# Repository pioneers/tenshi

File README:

Pioneers in Engineering Control System Next

STUFF

--------------------------------------------------------------------------------
- Hints for compiling and running                                              -
--------------------------------------------------------------------------------

Are you on Ubuntu? Use install_build_deps.sh! (You must be connected to the
Internet for this to work.) After running install_build_deps.sh, you also need
to manually:
1) Run emcc. This creates some config files necessary for it to work.
2) Run EAGLE. This creates a directory in your home so that it doesn't prompt
   you while building (and stalling the build).

Compile using ./build.sh. Build results are in build/artifacts.

Run angel-player using ./run-angel-player (build.sh is not needed in this
case).

Things needed for compiling:
* coreutils, build-essential, etc.
* tar, bz2, etc.
* python (2.7 recommended)
* nodejs (currently using v0.10.26, from the chris-lea/node.js PPA)
* wget
* pep8
* jshint (install from npm, currently using 2.1.11)
* csslint (install from npm, currently using 0.10.0)
* project-tenshi-tools (get from Jenkins)
* emscripten (get from http://rqou.com/emscripten-bin-18apr2014.tar.bz2)
* avr-gcc (currently using the nonolith/avr-toolchain PPA)
* libX11, Xvfb
* EAGLE (currently using v6.5.0)
* Java JRE
* PyYAML

Running Angel Player: It is recommended to have a separate copy of xulrunner
located somewhere such as your home directory. The command you would need to use
would be something like:
~/xulrunner/xulrunner angel-player/src/application.ini -jsconsole -purgecaches

-purgecaches is required in order to debug JS in-tree (without building and
updating build ID).

If you are running on Ubuntu, make sure to add yourself to the dialout group to
access your USB serial port (usually /dev/ttyUSB0).

Setting up Angel Player debugger:
Angel Player can be debugged by using the Firefox remote debug tools that are
normally used to debug Thunderbird/Firefox OS. To enable this on the Firefox
side:
1. Open the developer tools (Ctrl+Shift+I)
2. Click the "Settings" sprocket in the top-left.
3. Under advanced, enable remote debugging (you may also need to enable chrome
   debugging).

To enable remote debugging in Angel Player, either launch the in-tree version
of the code or set "devtools.debugger.remote-enabled" and
"devtools.chrome.enabled" to "true" in about:config. If for some reason you
already have an application listening on port 6000 on your computer, you can
also change "devtools.debugger.remote-port" to an alternate port.

To connect the remote debugger, select "Tools>Web Developer>Connect..." in
Firefox. Set the host to localhost and the port to 6000 (unless you changed
the port above) and click connect. Until this is fixed, to debug JS, select
"Main Process" and to debug CSS select "chrome://angel-player/content/main.html"

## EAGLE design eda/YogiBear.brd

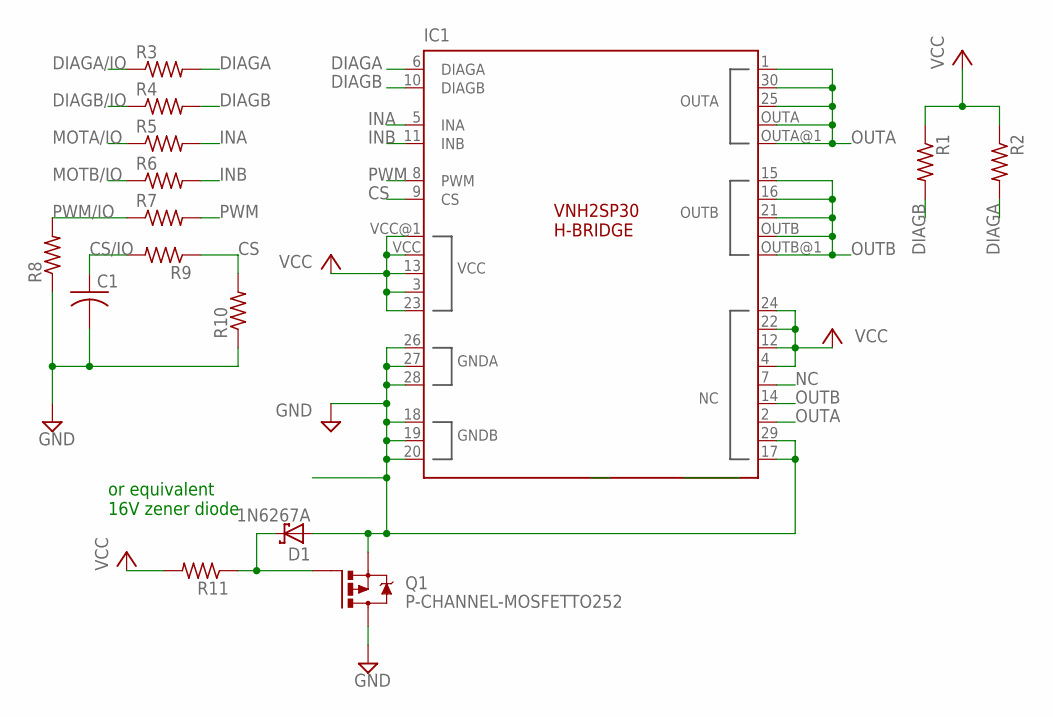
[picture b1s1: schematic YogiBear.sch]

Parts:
C1: C-US025-024X044; C025-024X044
D1: 1N6267A; C4111-15
IC1: VNH2SP30
Q1: P-CHANNEL-MOSFETTO252; TO252
R1, R2, R3, R4, R5, R6, R7, R8, R9, R10, R11: R-US_R0603; R0603

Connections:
CS: IC1.9 (CS), R9.1, R10.2
CS/IO: C1.1, R9.2
DIAGA: IC1.6 (DIAGA), R2.2, R3.2
DIAGA/IO: R3.1
DIAGB: IC1.10 (DIAGB), R1.2, R4.2
DIAGB/IO: R4.1
GND: C1.2, D1.A, IC1.17 (NC), IC1.18 (GNDB), IC1.19 (GNDB), IC1.20 (GNDB), IC1.26 (GNDA), IC1.27 (GNDA), IC1.28 (GNDA), IC1.29 (NC1), Q1.2 (S), Q1.3 (D), R8.1, R10.1
INA: IC1.5 (INA), R5.2
INB: IC1.11 (INB), R6.2
MOTA/IO: R5.1
MOTB/IO: R6.1
unnamed: D1.C, Q1.1 (G), R11.1
NC: IC1.7 (NC4)
OUTA: IC1.1 (OUTA), IC1.2 (NC2), IC1.25 (OUTA), IC1.30 (OUTA), IC1.OUTA, IC1.OUTA@1 (OUTA)
OUTB: IC1.14 (NC3), IC1.15 (OUTB), IC1.16 (OUTB), IC1.21 (OUTB), IC1.OUTB, IC1.OUTB@1 (OUTB)
PWM: IC1.8 (PWM), R7.2
PWM/IO: R7.1, R8.2
VCC: IC1.3 (VCC), IC1.13 (VCC), IC1.23 (VCC), IC1.VCC, IC1.VCC@1 (VCC), R1.1, R2.1, R11.2
VIN: IC1.4 (NC5), IC1.12 (NC6), IC1.22 (NC7), IC1.24 (NC8)

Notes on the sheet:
or equivalent 16V zener diode

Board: 2 copper layers, 15 parts (0 on the bottom side), 14 nets, no tracks yet.

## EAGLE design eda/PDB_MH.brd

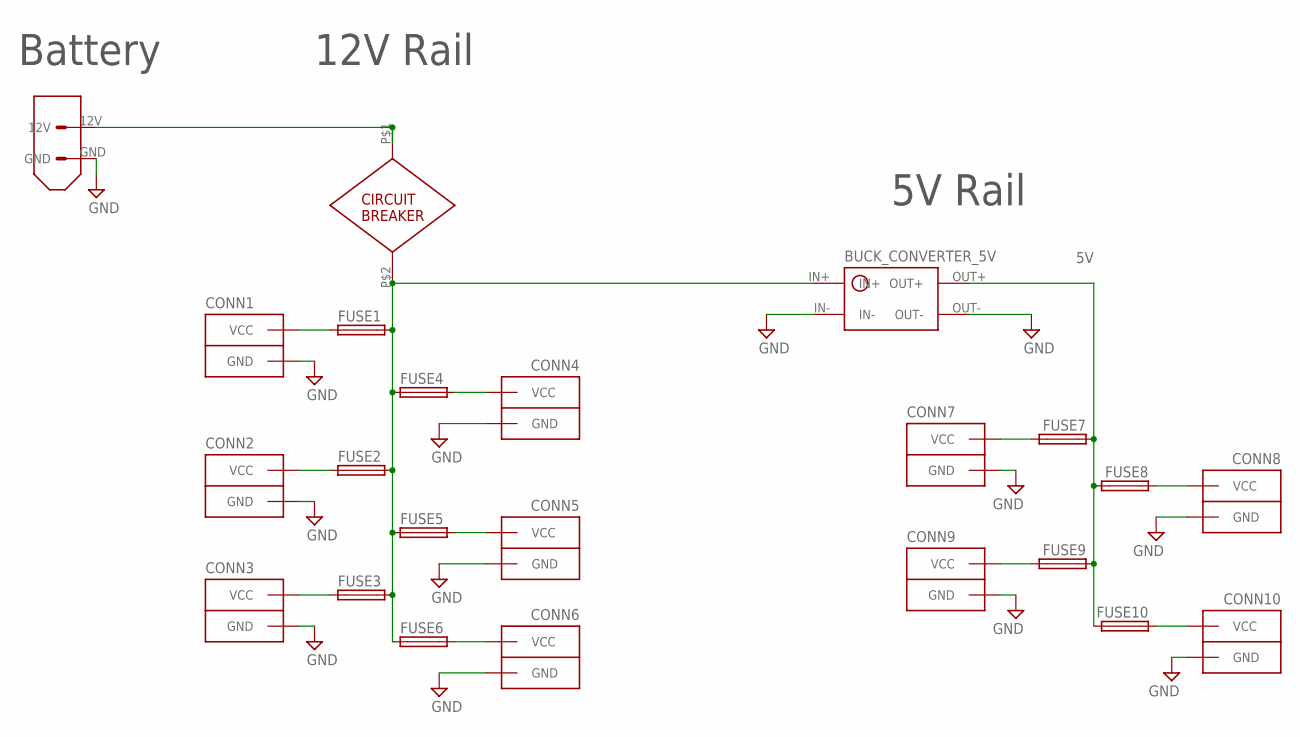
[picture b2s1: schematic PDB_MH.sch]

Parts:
CIRCUIT_BREAKER: CIRC_BREAKER
CONN1, CONN2, CONN3, CONN4, CONN5, CONN6, CONN7, CONN8, CONN9, CONN10: ANDERSONVERTICAL; ANDERSON_VERTICAL
FUSE1, FUSE2, FUSE3, FUSE4, FUSE5, FUSE6, FUSE7, FUSE8, FUSE9, FUSE10: FUSE_HOLDER_SMD
U$1: XT60CONNECTOR
U$7: BUCK_CONVERTER_5V

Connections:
5V: FUSE7.P$1_DOWN (1), FUSE7.P$1_UP (1), FUSE8.P$2_DOWN (2), FUSE8.P$2_UP (2), FUSE9.P$1_DOWN (1), FUSE9.P$1_UP (1), FUSE10.P$2_DOWN (2), FUSE10.P$2_UP (2), U$7.OUT+
12V: CIRCUIT_BREAKER.P$2, FUSE1.P$2_DOWN (2), FUSE1.P$2_UP (2), FUSE2.P$2_DOWN (2), FUSE2.P$2_UP (2), FUSE3.P$2_DOWN (2), FUSE3.P$2_UP (2), FUSE4.P$1_DOWN (1), FUSE4.P$1_UP (1), FUSE5.P$1_DOWN (1), FUSE5.P$1_UP (1), FUSE6.P$1_DOWN (1), FUSE6.P$1_UP (1), U$7.IN+
BAT: CIRCUIT_BREAKER.P$1, U$1.12V
GND: CONN1.PIN1 (GND), CONN2.PIN1 (GND), CONN3.PIN1 (GND), CONN4.PIN1 (GND), CONN5.PIN1 (GND), CONN6.PIN1 (GND), CONN7.PIN1 (GND), CONN8.PIN1 (GND), CONN9.PIN1 (GND), CONN10.PIN1 (GND), U$1.GND, U$7.IN-, U$7.OUT-
VOUT1: CONN1.PIN2 (VCC), FUSE1.P$1_DOWN (1), FUSE1.P$1_UP (1)
VOUT2: CONN2.PIN2 (VCC), FUSE2.P$1_DOWN (1), FUSE2.P$1_UP (1)
VOUT3: CONN3.PIN2 (VCC), FUSE3.P$1_DOWN (1), FUSE3.P$1_UP (1)
VOUT4: CONN4.PIN2 (VCC), FUSE4.P$2_DOWN (2), FUSE4.P$2_UP (2)
VOUT5: CONN5.PIN2 (VCC), FUSE5.P$2_DOWN (2), FUSE5.P$2_UP (2)
VOUT6: CONN6.PIN2 (VCC), FUSE6.P$2_DOWN (2), FUSE6.P$2_UP (2)
VOUT7: CONN7.PIN2 (VCC), FUSE7.P$2_DOWN (2), FUSE7.P$2_UP (2)
VOUT8: CONN8.PIN2 (VCC), FUSE8.P$1_DOWN (1), FUSE8.P$1_UP (1)
VOUT9: CONN9.PIN2 (VCC), FUSE9.P$2_DOWN (2), FUSE9.P$2_UP (2)
VOUT10: CONN10.PIN2 (VCC), FUSE10.P$1_DOWN (1), FUSE10.P$1_UP (1)

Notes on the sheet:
Battery
12V Rail
5V Rail

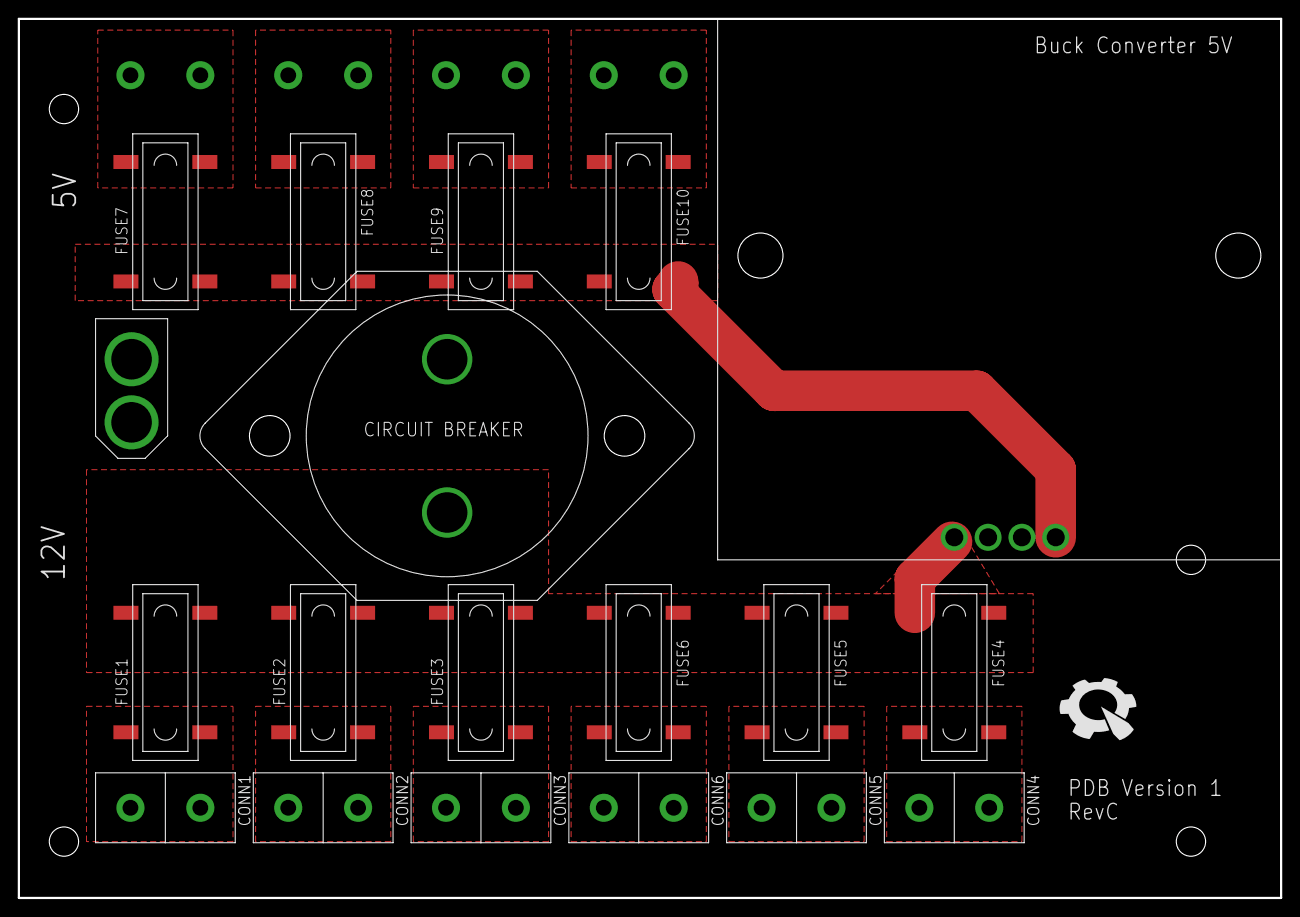
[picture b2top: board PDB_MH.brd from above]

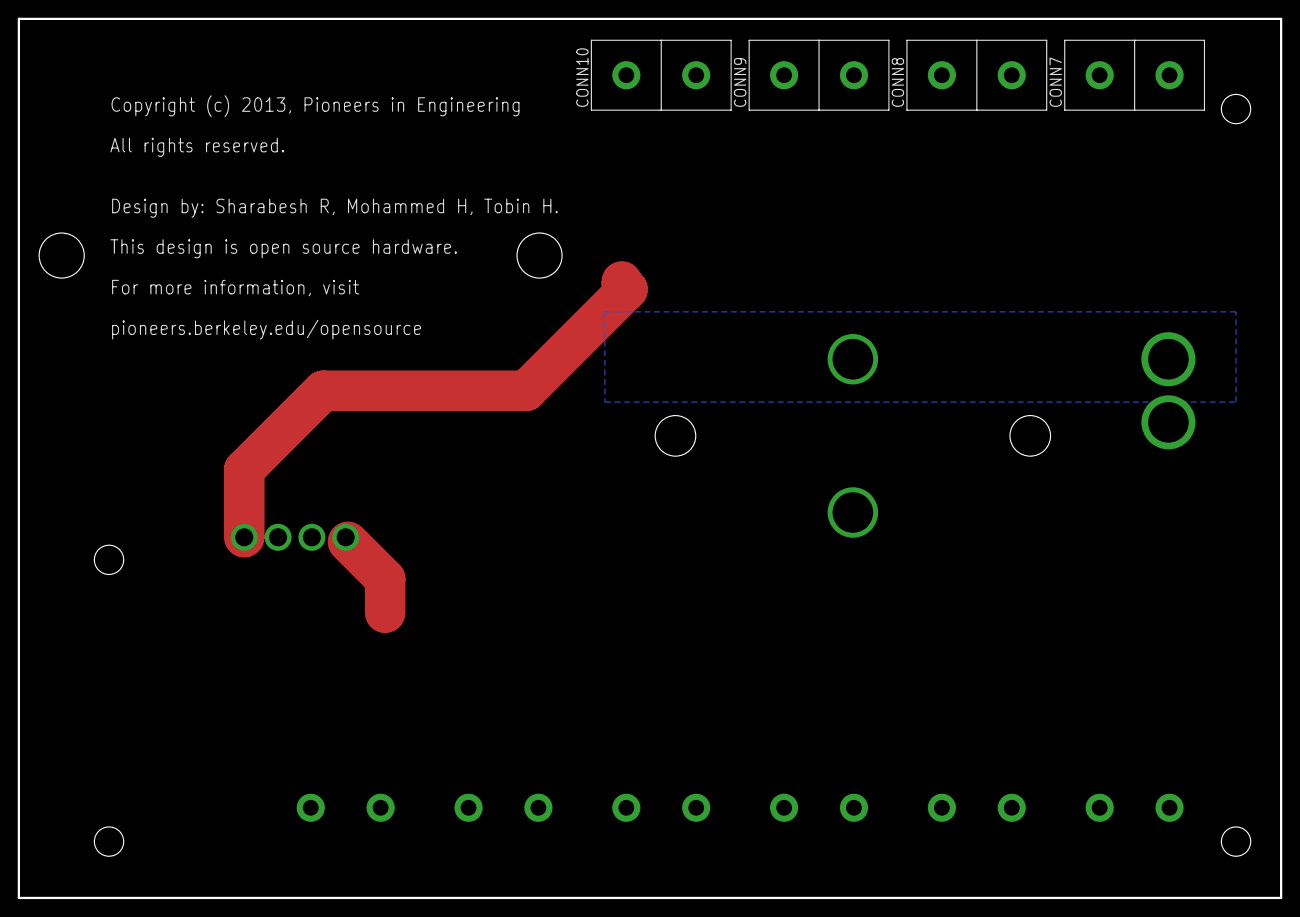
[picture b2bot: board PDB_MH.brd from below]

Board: 2 copper layers, 142.2 x 99.1 mm, 28 parts (5 on the bottom side), 14 nets.

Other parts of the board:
U$2, U$3, U$4, U$5: STAND-OFF
U$6: PIE-LOGO-SMALL

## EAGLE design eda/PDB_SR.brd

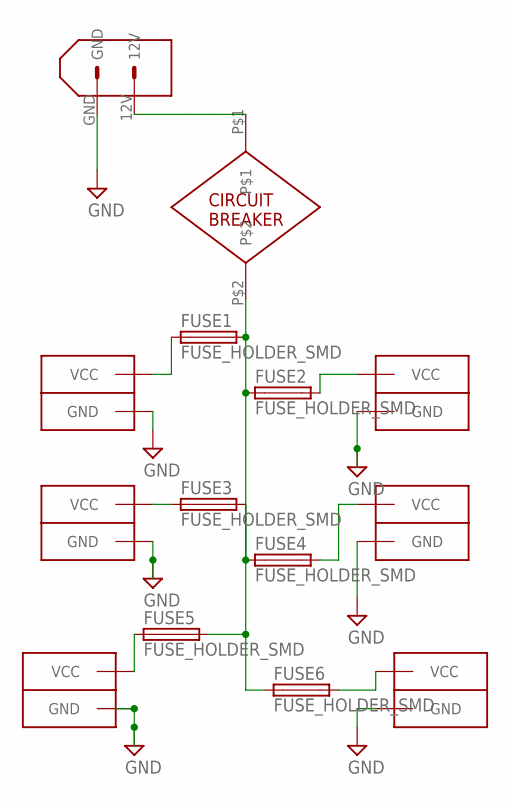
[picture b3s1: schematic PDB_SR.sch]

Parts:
CIRCUIT_BREAKER: CIRC_BREAKER
CONN1, CONN2, CONN3, CONN4, CONN5, CONN6: ANDERSONHORIZONTAL; ANDERSON_HORIZONTAL
FUSE1, FUSE2, FUSE3, FUSE4, FUSE5, FUSE6: FUSE_HOLDER_SMD
U$1: XT60CONNECTOR

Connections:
12V: CIRCUIT_BREAKER.P$2, FUSE1.P$2_DOWN (2), FUSE1.P$2_UP (2), FUSE2.P$1_DOWN (1), FUSE2.P$1_UP (1), FUSE3.P$2_DOWN (2), FUSE3.P$2_UP (2), FUSE4.P$1_DOWN (1), FUSE4.P$1_UP (1), FUSE5.P$2_DOWN (2), FUSE5.P$2_UP (2), FUSE6.P$1_DOWN (1), FUSE6.P$1_UP (1)
BAT: CIRCUIT_BREAKER.P$1, U$1.12V
GND: CONN1.PIN1 (GND), CONN1.PIN1-LEAD (GND), CONN2.PIN1 (GND), CONN2.PIN1-LEAD (GND), CONN3.PIN1 (GND), CONN3.PIN1-LEAD (GND), CONN4.PIN1 (GND), CONN4.PIN1-LEAD (GND), CONN5.PIN1 (GND), CONN5.PIN1-LEAD (GND), CONN6.PIN1 (GND), CONN6.PIN1-LEAD (GND), U$1.GND
VOUT1: CONN2.PIN2 (VCC), CONN2.PIN2-LEAD (VCC), FUSE1.P$1_DOWN (1), FUSE1.P$1_UP (1)
VOUT2: CONN4.PIN2 (VCC), CONN4.PIN2-LEAD (VCC), FUSE2.P$2_DOWN (2), FUSE2.P$2_UP (2)
VOUT3: CONN1.PIN2 (VCC), CONN1.PIN2-LEAD (VCC), FUSE3.P$1_DOWN (1), FUSE3.P$1_UP (1)
VOUT4: CONN5.PIN2 (VCC), CONN5.PIN2-LEAD (VCC), FUSE4.P$2_DOWN (2), FUSE4.P$2_UP (2)
VOUT5: CONN3.PIN2 (VCC), CONN3.PIN2-LEAD (VCC), FUSE5.P$1_DOWN (1), FUSE5.P$1_UP (1)
VOUT6: CONN6.PIN2 (VCC), CONN6.PIN2-LEAD (VCC), FUSE6.P$2_DOWN (2), FUSE6.P$2_UP (2)

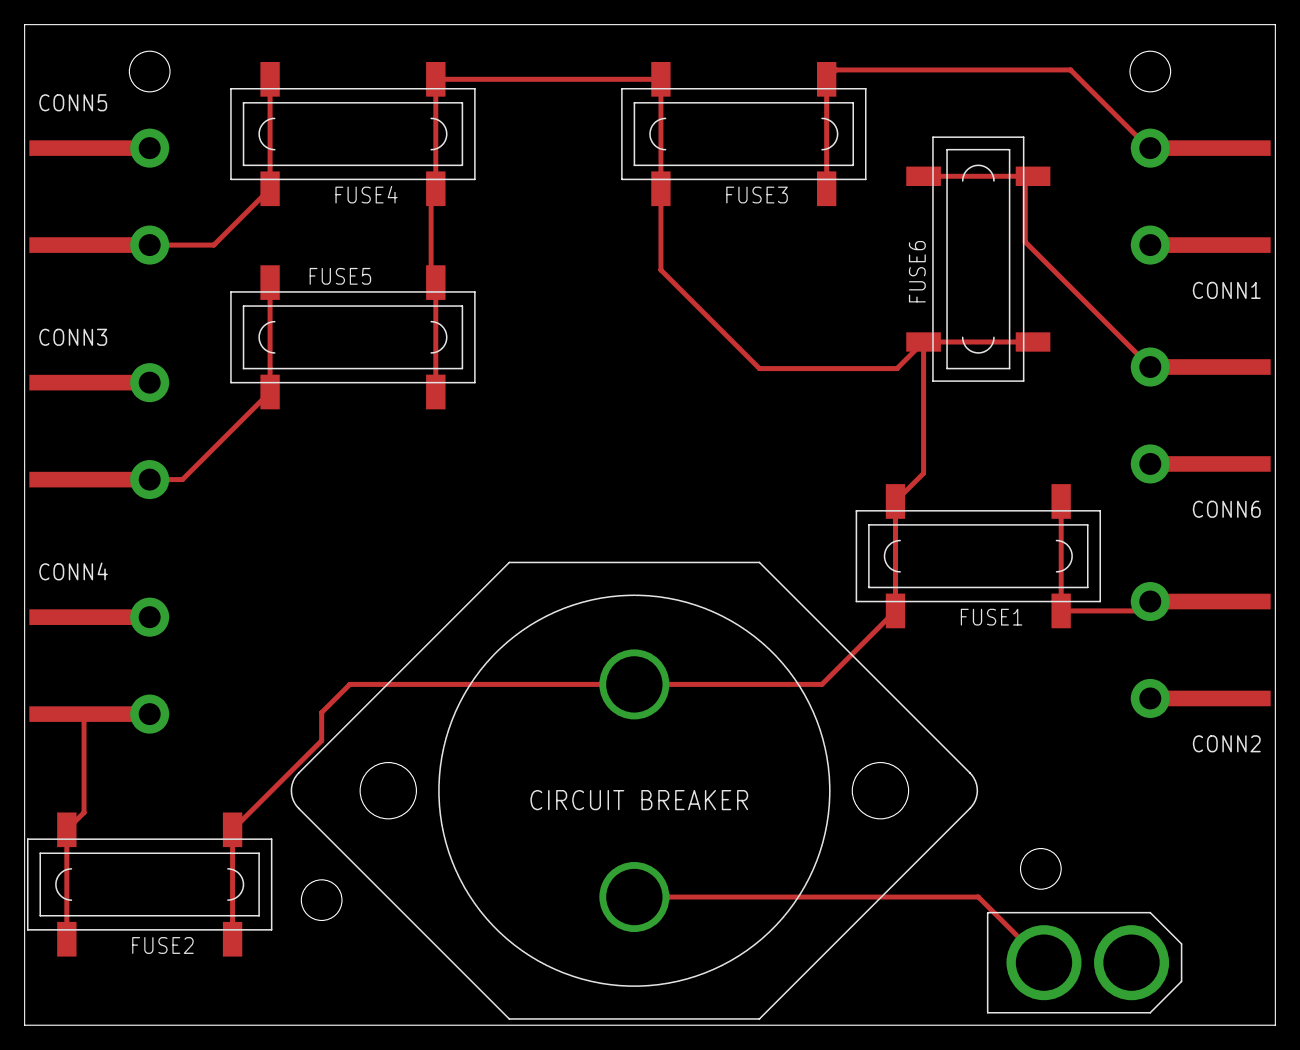
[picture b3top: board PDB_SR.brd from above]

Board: 2 copper layers, 101.6 x 81.3 mm, 18 parts (0 on the bottom side), 9 nets.

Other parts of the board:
U$2, U$3, U$4, U$5: STAND-OFF

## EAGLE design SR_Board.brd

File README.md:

Pioneers in Engineering Control System Next
===========================================

## UI Development Quick-Start (Angel-Player)
The following steps should work on Linux, OS X, and Windows (cygwin).

1. Install `firefox` (v30+), `git` (which comes with cygwin / git bash on
Windows).
2. `git clone [this repo]`
3. Run `dev.sh`
4. There's no need to run `build.sh`
5. Reload Angel-Player without restarting it by clicking the square at the
   bottom right, and clicking the `Reload` text that appears.
6. To interact with a robot or run code in the simulator, for the time being
   the Slow-Start is needed (or the artifacts from it).

## Windows
If you're on Windows and can't run `dev.sh` (not using cygwin), run `dev.bat`

## UI Development Slow-Start (and release build instructions)
1. Install essential and angel-player dependencies below.
2. Run `build-angel-player.sh` once.
3. Run `./run-angel-player` or `./dev.sh` without `build.sh` to see changes.

## Building the Whole System
1. Install all dependencies below.
2. Run `build.sh`.

## Setting up Angel Player debugger
Angel Player can be debugged by using the Firefox remote debug tools that are
normally used to debug Thunderbird/Firefox OS. To enable this on the Firefox
side:

1. Open the developer tools (Ctrl+Shift+I)
2. Click the "Settings" sprocket in the top-left.
3. Under advanced, enable remote debugging (you may also need to enable chrome
   debugging).

To enable remote debugging in Angel Player, either launch the in-tree version
of the code (`./run-angel-player` or `./dev.sh`) or set
"devtools.debugger.remote-enabled" and "devtools.chrome.enabled" to "true" in
about:config. If for some reason you already have an application listening on
port 6000 on your computer, you can also change "devtools.debugger.remote-port"
to an alternate port.

To connect the remote debugger, restart firefox and select `Tools->Web
Developer->Connect...` in Firefox. Set the host to localhost and the port to
6000 (unless you changed the port above) and click connect. Select `Main
Process` from the list that appears.

## Full System Setup (i.e. how to run build.sh)
Are you on Ubuntu? Use `install_build_deps.sh`! (You must be connected to the
Internet for this to work.) After running install_build_deps.sh, you also need
to manually:

1. Run emcc. This creates some config files necessary for it to work.
2. Run EAGLE. This creates a directory in your home so that it doesn't prompt
   you while building (and stalling the build).
3. If you are running on Ubuntu, make sure to add yourself to the dialout group to
   access your USB serial port (usually /dev/ttyUSB0). This can be done using
   the command `sudo useradd -G dialout $USER`
4. The whole build system can be run using `./build.sh`. Build results are in
   build/artifacts.

If you're not on Ubuntu, it's more difficult. Basically, install the
equivalents of the dependencies below.

## Full System Dependencies

For the time being, `build.sh` is not modular enough, and needs all of these
dependencies to exist to do anything.

However, Angel-Player can be built with only its listed dependencies using
`./build-angel-player.sh`.

### To do anything
* PyYAML
* coreutils, build-essential, etc.
* python (2.7 recommended)
* tar, bz2, etc.
* wget

### To build release Angel-Player
* emscripten (get from http://rqou.com/emscripten-bin-18apr2014.tar.bz2)

### To lint Angel-Player
* nodejs (currently using v0.10.26, from the chris-lea/node.js PPA)
* jshint (install from npm, currently using 2.1.11)
* csslint (install from npm, currently using 0.10.0)
* Java JRE

### To test Angel-Player
* libX11, Xvfb (also used to build eda)

### To build eda
* EAGLE (currently using v6.5.0)
* libX11, Xvfb (also used to test Angel-Player)

### To build embedded software
* project-tenshi-tools (get from Jenkins)
* avr-gcc (currently using the nonolith/avr-toolchain PPA)

### To lint the build system itself
* pep8

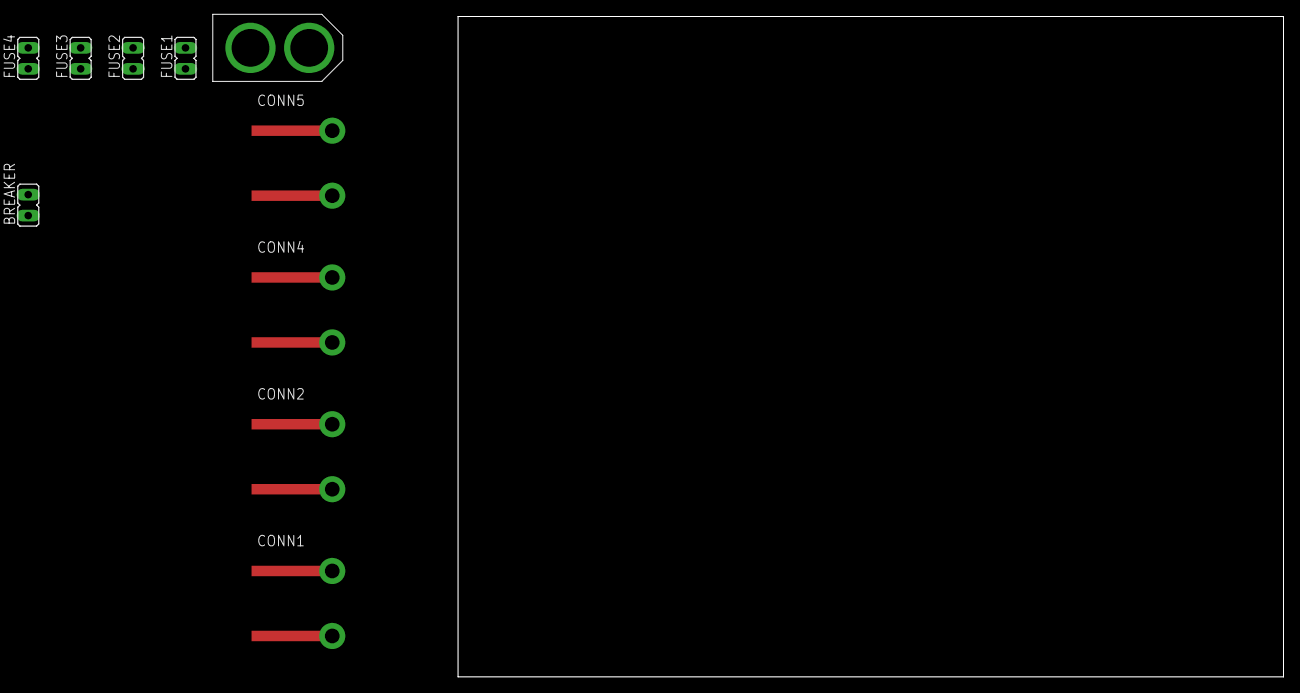
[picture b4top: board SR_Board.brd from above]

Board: 2 copper layers, 100.0 x 80.0 mm, 10 parts (0 on the bottom side), 8 nets, no tracks yet.

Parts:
BREAKER: JP1
CONN1, CONN2, CONN4, CONN5: ANDERSONHORIZONTAL; ANDERSON_HORIZONTAL
FUSE1, FUSE2, FUSE3, FUSE4: JP1
U$1: XT60CONNECTOR

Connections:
12V: BREAKER.1, BREAKER.2, FUSE1.2, FUSE3.1, FUSE4.2, U$1.12V
GND: CONN2.PIN1, CONN2.PIN1-LEAD, CONN5.PIN1, CONN5.PIN1-LEAD, U$1.GND
unnamed: CONN2.PIN2, CONN2.PIN2-LEAD, FUSE1.1
unnamed: CONN1.PIN2, CONN1.PIN2-LEAD
unnamed: CONN5.PIN2, CONN5.PIN2-LEAD, FUSE4.1
unnamed: CONN4.PIN2, CONN4.PIN2-LEAD, FUSE3.2
unnamed: CONN4.PIN1, CONN4.PIN1-LEAD
unnamed: CONN1.PIN1, CONN1.PIN1-LEAD

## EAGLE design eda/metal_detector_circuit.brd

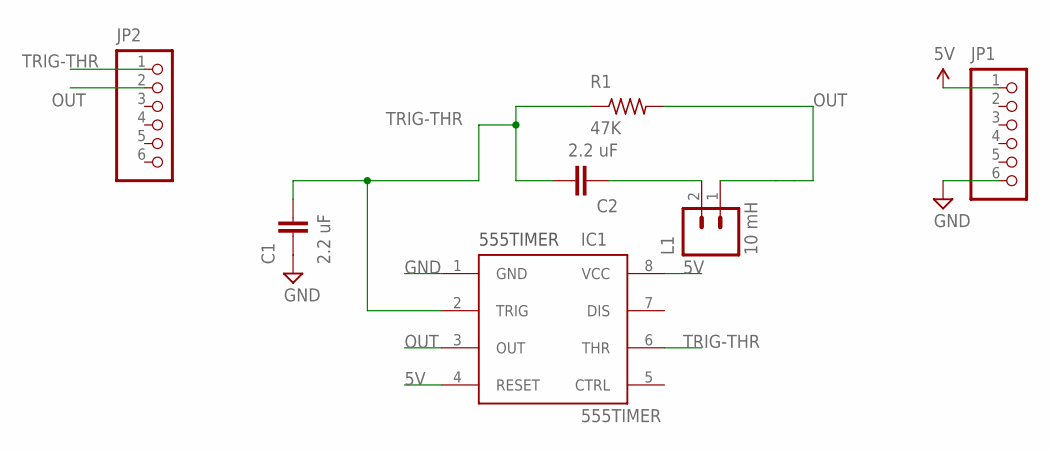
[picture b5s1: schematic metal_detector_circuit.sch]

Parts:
C1, C2: 2.2 uF; 0603-CAP
IC1: 555TIMER; 8-PIN_SOIC
JP1, JP2: PINHD-1X6; 1X06
L1: 10 mH; 1X02
R1: 47K; R0603

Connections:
5V: IC1.4 (RESET), IC1.8 (VCC), JP1.1
GND: C1.1, IC1.1 (GND), JP1.6
unnamed: C2.1, L1.2
OUT: IC1.3 (OUT), JP2.2, L1.1, R1.2
TRIG-THR: C1.2, C2.2, IC1.2 (TRIG), IC1.6 (THR), JP2.1, R1.1

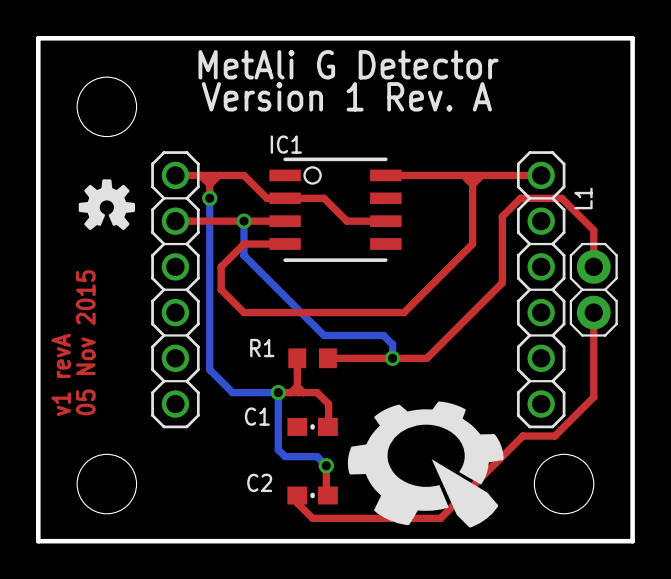
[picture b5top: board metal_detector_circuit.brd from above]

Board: 2 copper layers, 33.0 x 27.9 mm, 12 parts (0 on the bottom side), 5 nets.

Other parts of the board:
U$1: PIE-LOGO-SMALL
U$2, U$4, U$17: STAND-OFF
U$7: OSHW-LOGO-S

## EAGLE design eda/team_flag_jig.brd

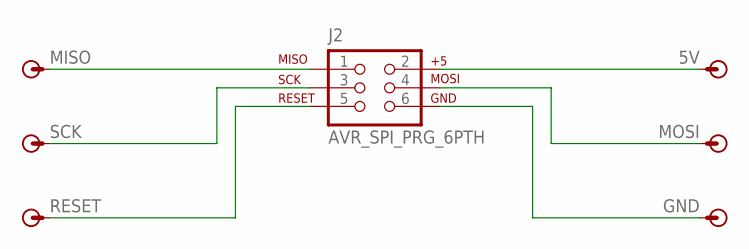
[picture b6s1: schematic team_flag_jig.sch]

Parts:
5V: POGO_PIN; POGO_PIN_394
GND: POGO_PIN; POGO_PIN_394
J2: AVR_SPI_PRG_6PTH; 2X3
MISO: POGO_PIN; POGO_PIN_394
MOSI: POGO_PIN; POGO_PIN_394
RESET: POGO_PIN; POGO_PIN_394
SCK: POGO_PIN; POGO_PIN_394

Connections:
5V: 5V.POGO_PIN, J2.2
A: GND.POGO_PIN, J2.6
MISO: J2.1, MISO.POGO_PIN
MOSI: J2.4, MOSI.POGO_PIN
RESET: J2.5, RESET.POGO_PIN
SCK: J2.3, SCK.POGO_PIN

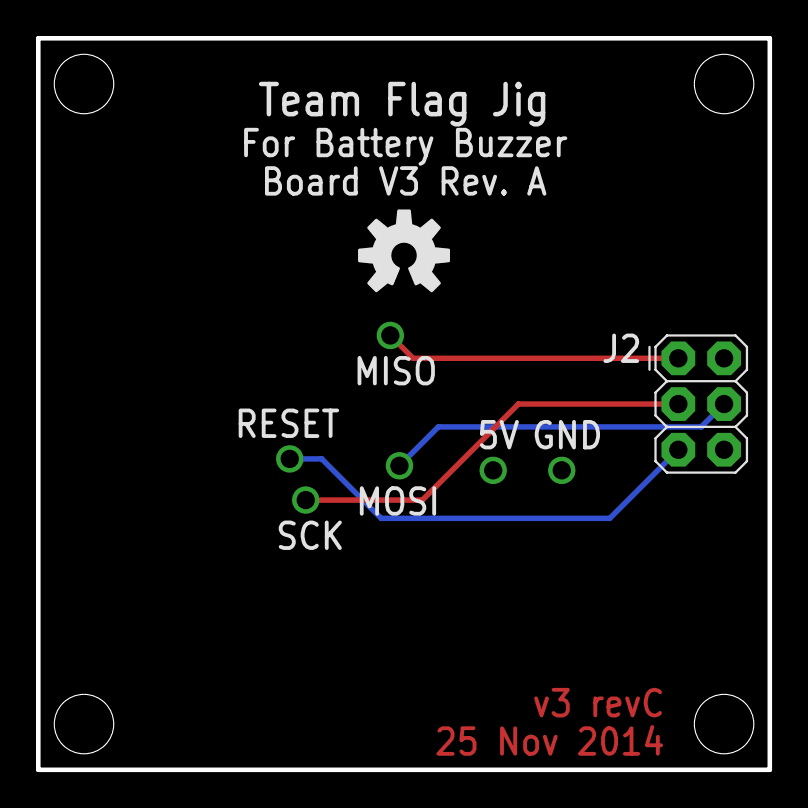
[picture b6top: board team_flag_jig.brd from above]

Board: 2 copper layers, 40.6 x 40.6 mm, 13 parts (1 on the bottom side), 6 nets.

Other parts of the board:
U$1: OSHW-LOGO-M
U$2: PIE-LOGO-SMALL
U$3, U$4, U$5, U$6: STAND-OFF

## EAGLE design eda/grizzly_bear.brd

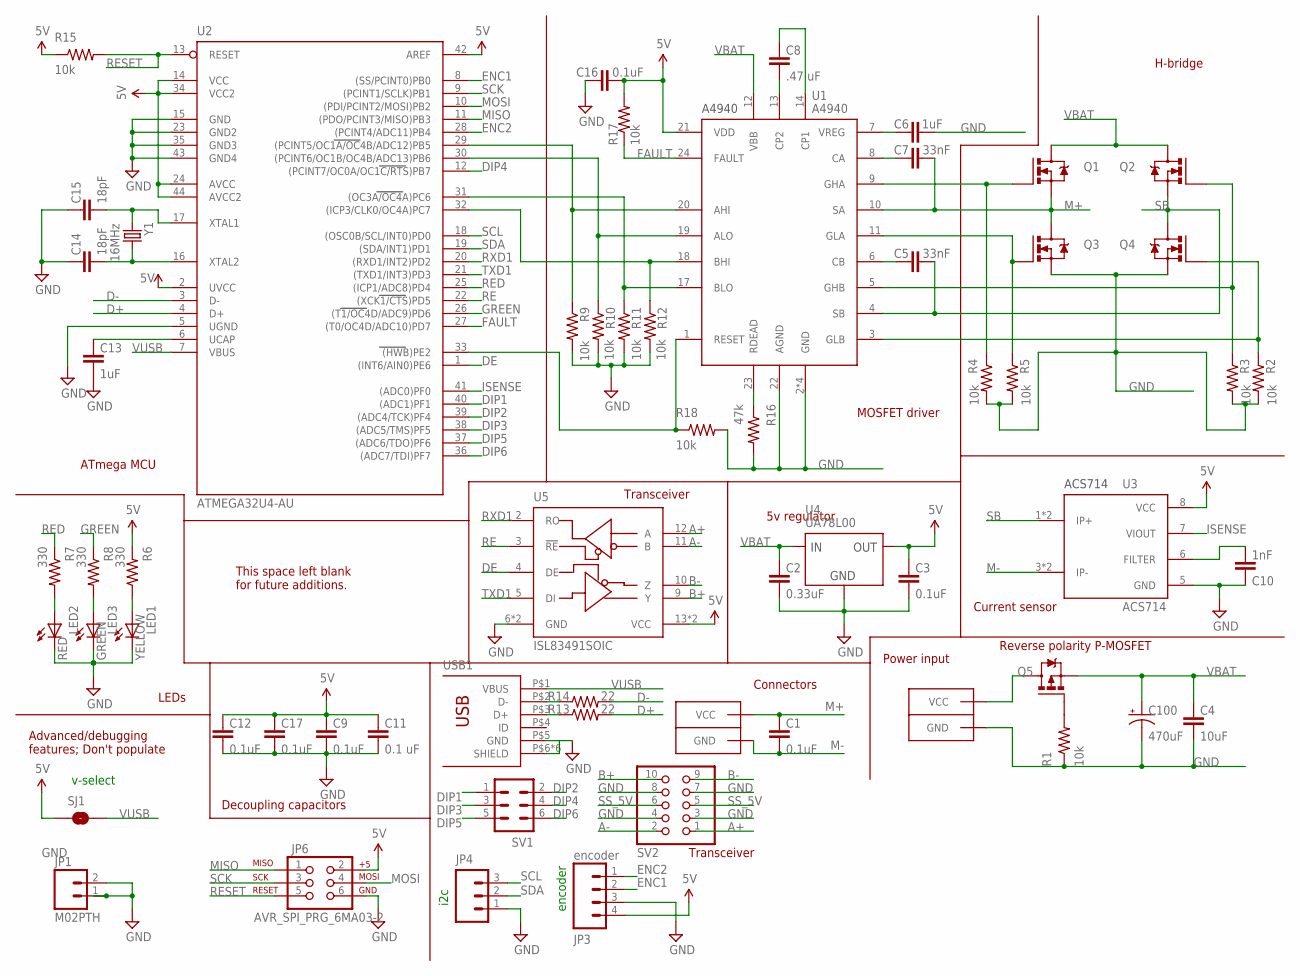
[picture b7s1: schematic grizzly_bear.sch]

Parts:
C1, C3, C9, C12, C16, C17: 0.1uF; 0603-CAP
C2: 0.33uF; 0603-CAP
C4: 10uF; 1206
C5, C7: 33nF; 0603-CAP
C6, C13: 1uF; 0603-CAP
C8: .47 uF; 0603-CAP
C10: 1nF; 0603-CAP
C11: 0.1 uF; 0603-CAP
C14, C15: 18pF; 0603-CAP
C100: 470uF; PANASONIC_G
JP1: M02PTH; 1X02
JP3: encoder; 1X04-MTA
JP4: M031X03-MTA; 1X03-MTA
JP6: AVR_SPI_PRG_6MA03-2; MA03-2
LED1: YELLOW; LED-0805
LED2: RED; LED-0805
LED3: GREEN; LED-0805
Q1, Q2, Q3, Q4: PSMN4R0; SOT669
Q5: IPD90P03P4L; TO252
R1, R2, R3, R4, R5, R9, R10, R11, R12, R15, R17, R18: 10k; R0603
R6, R7, R8: 330; R0603
R13, R14: 22; R0603
R16: 47k; R0603
SJ1: SOLDERJUMPERNO; SJ_2S-NO
SV1: MA03-2
SV2: SENSOR_CON_5PINPTH-SHROUDED; 2X5_SHROUDED
U1: A4940; 24-PIN_TSSOP
U2: ATMEGA32U4-AU; TQFP44
U3: ACS714; 8-PIN_SOIC
U4: UA78L00; SOT-89-3
U5: ISL83491SOIC; SOIC14
U$18, U$19: ANDERSONVERTICAL; ANDERSON_VERTICAL
USB1: USB-OTGMICRO-AB; USB-MICRO-AB
Y1: 16MHz; HC49UP

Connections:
5V: C3.1, C9.1, C11.2, C12.1, C16.1, C17.1, JP3.4, JP6.2, R6.2, R15.1, R17.2, SJ1.1, U1.21 (VDD), U2.2 (UVCC), U2.14 (VCC), U2.24 (AVCC), U2.34 (VCC2), U2.42 (AREF), U2.44 (AVCC2), U3.8 (VCC), U4.OUTPUT (OUT), U5.13 (VCC), U5.14 (VCC)
A+: SV2.1, U5.12 (A)
A-: SV2.2, U5.11 (B)
AHI: R9.1, U1.20 (AHI), U2.29 ((PCINT5/OC1A/OC4B/ADC12)PB5)
ALO: R10.1, U1.19 (ALO), U2.30 ((PCINT6/OC1B/OC4B/ADC13)PB6)
B+: SV2.10, U5.9 (Y)
B-: SV2.9, U5.10 (Z)
BHI: R12.1, U1.18 (BHI), U2.32 ((ICP3/CLK0/OC4A)PC7)
BLO: R11.1, U1.17 (BLO), U2.31 ((OC3A/OC4A)PC6)
CA: C7.1, U1.8 (CA)
CB: C5.2, U1.6 (CB)
CP1: C8.1, U1.14 (CP1)
CP2: C8.2, U1.13 (CP2)
D+: R13.2, U2.4 (D+)
D+-_CON: R13.1, USB1.P$3 (D+)
D-: R14.2, U2.3 (D-)
D-_CON: R14.1, USB1.P$2 (D-)
DE: U2.1 ((INT6/AIN0)PE6), U5.4 (DE)
DIP1: SV1.1, U2.40 ((ADC1)PF1)
DIP2: SV1.2, U2.39 ((ADC4/TCK)PF4)
DIP3: SV1.3, U2.38 ((ADC5/TMS)PF5)
DIP4: SV1.4, U2.12 ((PCINT7/OC0A/OC1C/RTS)PB7)
DIP5: SV1.5, U2.37 ((ADC6/TDO)PF6)
DIP6: SV1.6, U2.36 ((ADC7/TDI)PF7)
DRIVER-RESET: R18.1, U1.1 (RESET), U2.33 ((HWB)PE2)
ENC1: JP3.2, U2.8 ((SS/PCINT0)PB0)
ENC2: JP3.1, U2.28 ((PCINT4/ADC11)PB4)
FAULT: R17.1, U1.24 (FAULT), U2.27 ((T0/OC4D/ADC10)PD7)
FILTER: C10.2, U3.6 (FILTER)
GHA: Q1.4 (G), R4.1, U1.9 (GHA)
GHB: Q2.4 (G), R3.1, U1.5 (GHB)
GLA: Q3.4 (G), R5.1, U1.11 (GLA)
GLB: Q4.4 (G), R2.1, U1.3 (GLB)
GND: C2.2, C3.2, C4.1, C6.2, C9.2, C10.1, C11.1, C12.2, C13.2, C14.1, C15.1, C16.2, C17.2, C100.-, JP1.1, JP1.2, JP3.3, JP4.1, JP6.6, LED1.C, LED2.C, LED3.C, Q3.1 (S), Q3.2 (S), Q3.3 (S), Q4.1 (S), Q4.2 (S), Q4.3 (S), R1.1, R2.2, R3.2, R4.2, R5.2, R9.2, R10.2, R11.2, R12.2, R16.2, R18.2, SV2.3, SV2.4, SV2.7, SV2.8, U1.2 (GND), U1.15 (GND), U1.16 (GND), U1.22 (AGND), U1.PAD (GND), U2.5 (UGND), U2.15 (GND), U2.23 (GND2), U2.35 (GND3), U2.43 (GND4), U3.5 (GND), U4.COMMON (GND), U5.6 (GND), U5.7 (GND), U$18.PIN1 (GND), USB1.P$5 (GND), USB1.P$6 (SHIELD), USB1.P$7 (SHIELD), USB1.P$8 (SHIELD), USB1.P$9 (SHIELD), USB1.P$10 (SHIELD), USB1.P$11 (SHIELD)
GREEN: R8.1, U2.26 ((T1/OC4D/ADC9)PD6)
GREEN-LED: LED3.A, R8.2
ISENSE: U2.41 ((ADC0)PF0), U3.7 (VIOUT)
M+: C1.1, C7.2, Q1.1 (S), Q1.2 (S), Q1.3 (S), Q3.MB (D), U1.10 (SA), U$19.PIN2 (VCC)
M-: C1.2, U3.3 (IP-), U3.4 (IP-), U$19.PIN1 (GND)
MISO: JP6.1, U2.11 ((PDO/PCINT3/MISO)PB3)
MOSI: JP6.4, U2.10 ((PDI/PCINT2/MOSI)PB2)
POWER-LED: LED1.A, R6.1
RDEAD: R16.1, U1.23 (RDEAD)
RE: U2.22 ((XCK1/CTS)PD5), U5.3 (!RE)
RED: R7.1, U2.25 ((ICP1/ADC8)PD4)
RED-LED: LED2.A, R7.2
RESET: JP6.5, R15.2, U2.13 (RESET)
RPP-GATE: Q5.1 (G), R1.2
RXD1: U2.20 ((RXD1/INT2)PD2), U5.2 (RO)
SB: C5.1, Q2.1 (S), Q2.2 (S), Q2.3 (S), Q4.MB (D), U1.4 (SB), U3.1 (IP+), U3.2 (IP+)
SCK: JP6.3, U2.9 ((PCINT1/SCLK)PB1)
SCL: JP4.3, U2.18 ((OSC0B/SCL/INT0)PD0)
SDA: JP4.2, U2.19 ((SDA/INT1)PD1)
SS_5V: SV2.5, SV2.6
TXD1: U2.21 ((TXD1/INT3)PD3), U5.5 (DI)
UCAP: C13.1, U2.6 (UCAP)
VBAT: C2.1, C4.2, C100.+, Q1.MB (D), Q2.MB (D), Q5.2 (S), U1.12 (VBB), U4.INPUT (IN)
VIN: Q5.3 (D), U$18.PIN2 (VCC)
VREG: C6.1, U1.7 (VREG)
VUSB: SJ1.2, U2.7 (VBUS), USB1.P$1 (VBUS)
XTAL1: C15.2, U2.17 (XTAL1), Y1.2
XTAL2: C14.2, U2.16 (XTAL2), Y1.1

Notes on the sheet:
v-select
i2c
encoder
Advanced/debugging features; Don't populate
Connectors
Decoupling capacitors
LEDs
ATmega MCU
MOSFET driver
H-bridge
Current sensor
5v regulator
Power input
Reverse polarity P-MOSFET
Transceiver
This space left blank for future additions.

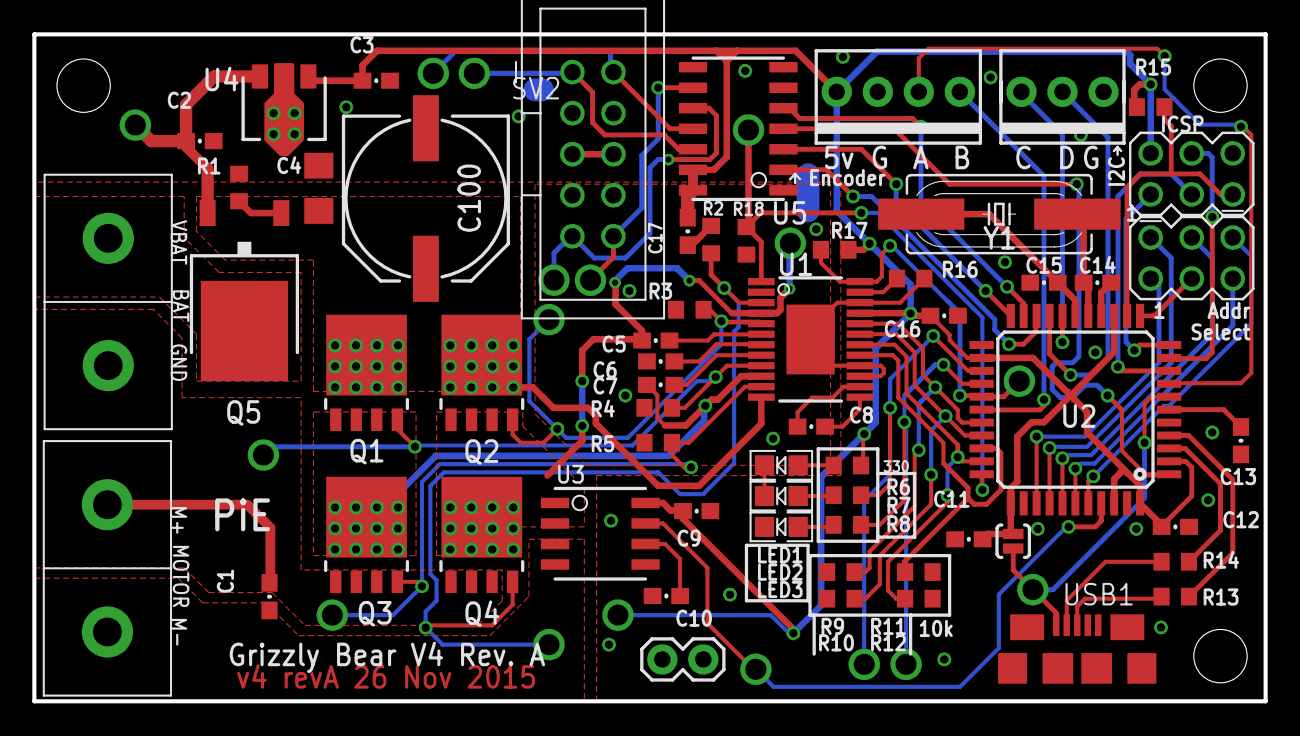
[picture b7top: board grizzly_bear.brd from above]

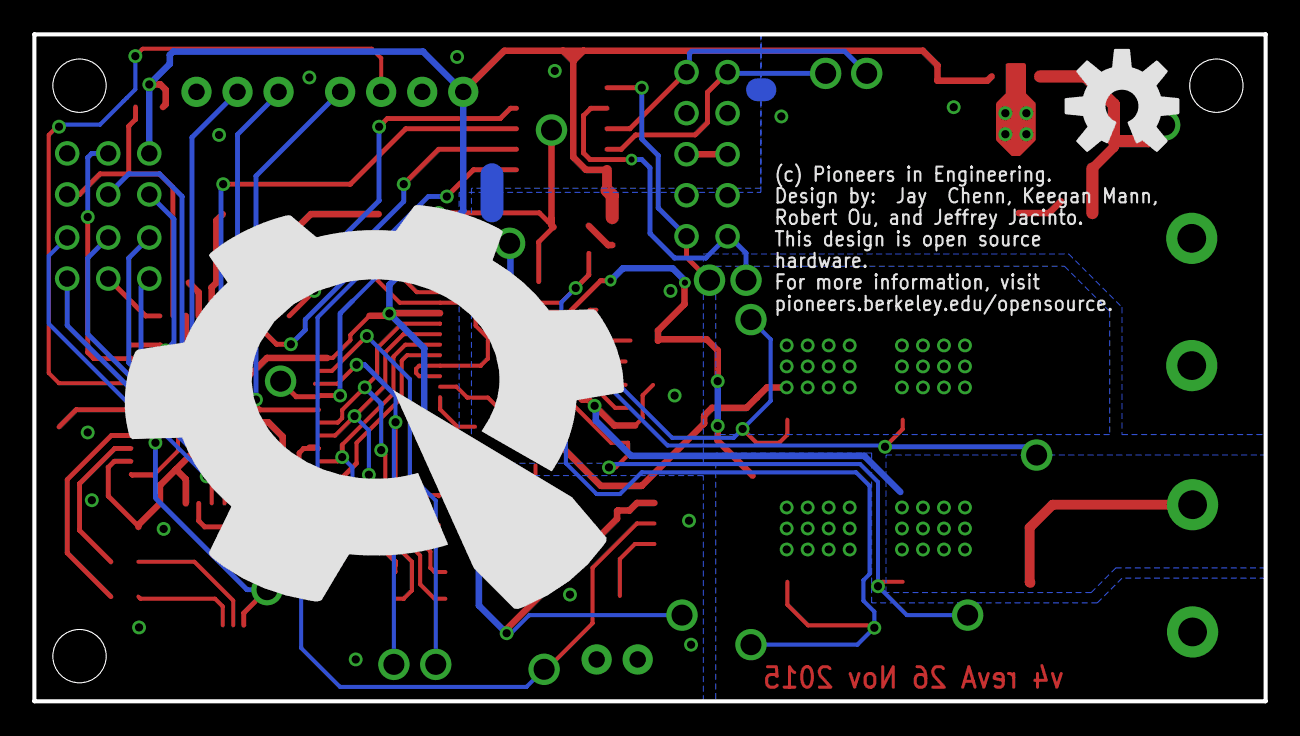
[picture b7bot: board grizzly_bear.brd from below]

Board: 2 copper layers, 76.2 x 41.3 mm, 65 parts (2 on the bottom side), 62 nets.

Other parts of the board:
STANDOFF1, STANDOFF2, STANDOFF3: STAND-OFF
U$1: OSHW-LOGO-L
U$17: PIE-LOGO

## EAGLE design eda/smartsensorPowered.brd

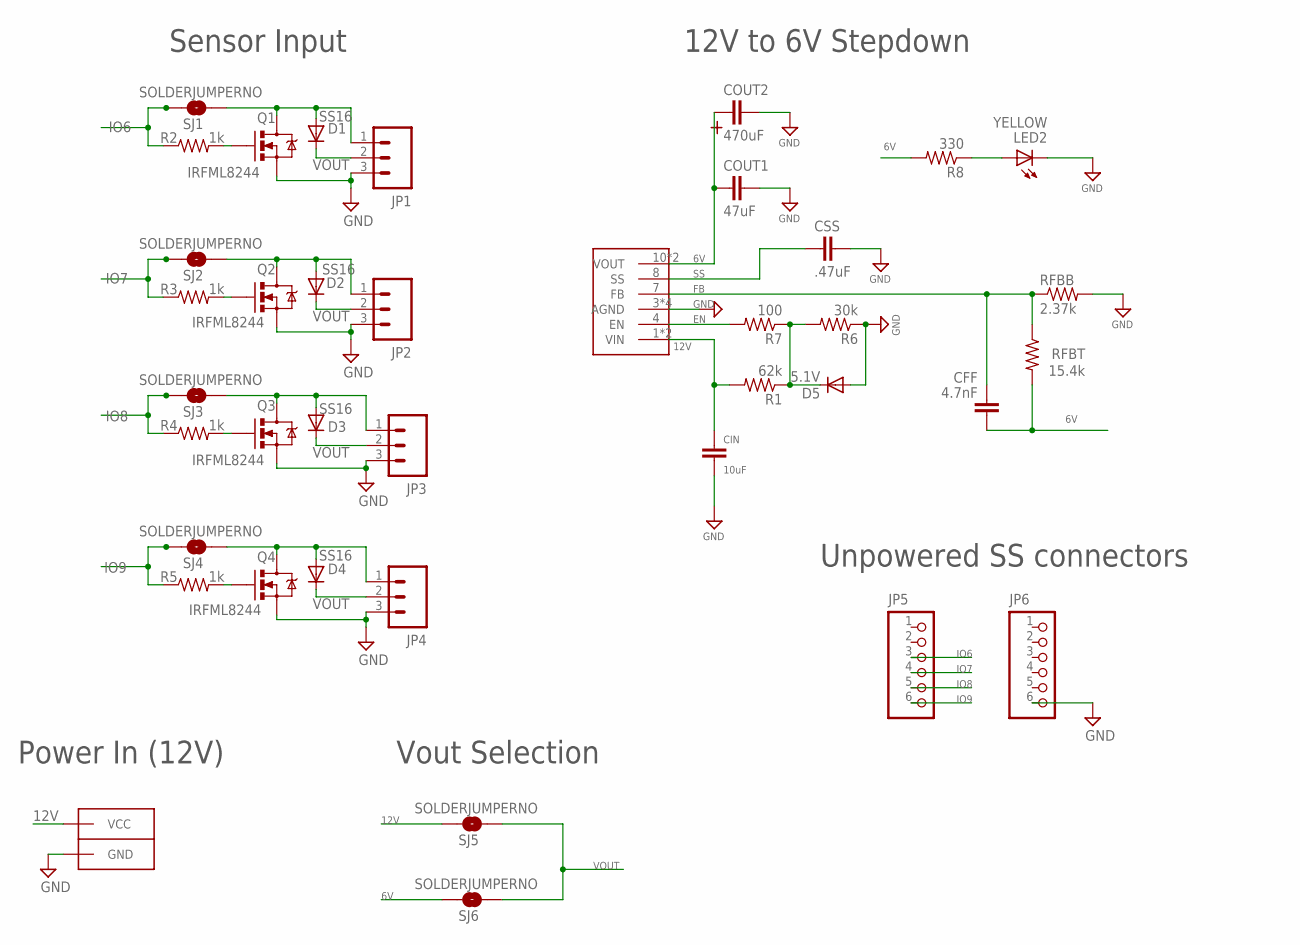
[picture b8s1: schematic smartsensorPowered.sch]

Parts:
CFF: 4.7nF; 0603-CAP
CIN: 10uF; 1206
CONN1: ANDERSONVERTICAL; ANDERSON_VERTICAL
COUT1: 47uF; 1206
COUT2: 470uF; TANT_CASE_E
CSS: .47uF; 0603-CAP
D1, D2, D3, D4: SS16; SMA-DIODE_ALT
D5: 5.1V; SOD-323
JP1, JP2, JP3, JP4: M031X03-MTA; 1X03-MTA
JP5, JP6: PINHD-1X6; 1X06
LED2: YELLOW; LED-0805
Q1, Q2, Q3, Q4: IRFML8244; SOT23-3
R1: 62k; R0603
R2, R3, R4, R5: 1k; R0603
R6: 30k; R0603
R7: 100; R0603
R8: 330; R0603
RFBB: 2.37k; R0603
RFBT: 15.4k; R0603
SJ1, SJ2, SJ3, SJ4, SJ5, SJ6: SOLDERJUMPERNO; SJ_2S-NO
U$3: LMZ12010

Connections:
6V: CFF.1, COUT1.1, COUT2.POS, R8.2, RFBT.2, SJ6.1, U$3.10 (VOUT), U$3.11 (VOUT)
6V_IF_SERVO1: D1.A, JP1.1, Q1.3 (D), SJ1.2
6V_IF_SERVO2: D2.A, JP2.1, Q2.3 (D), SJ2.2
6V_IF_SERVO3: D3.A, JP3.1, Q3.3 (D), SJ3.2
6V_IF_SERVO4: D4.A, JP4.1, Q4.3 (D), SJ4.2
12V: CIN.1, CONN1.PIN2 (VCC), R1.2, SJ5.1, U$3.1 (VIN), U$3.2 (VIN)
DIODE: D5.2 (C), R1.1, R6.2, R7.1
EN: R7.2, U$3.4 (EN)
FB: CFF.2, RFBB.1, RFBT.1, U$3.7 (FB)
GND: CIN.2, CONN1.PIN1 (GND), COUT1.2, COUT2.NEG, CSS.2, D5.1 (A), JP1.3, JP2.3, JP3.3, JP4.3, JP6.6, LED2.C, Q1.2 (S), Q2.2 (S), Q3.2 (S), Q4.2 (S), R6.1, RFBB.2, U$3.3 (AGND), U$3.5 (AGND), U$3.6 (AGND), U$3.GND (AGND)
IO6: JP5.3, R2.1, SJ1.1
IO7: JP5.4, R3.1, SJ2.1
IO8: JP5.5, R4.1, SJ3.1
IO9: JP5.6, R5.1, SJ4.1
unnamed: Q1.1 (G), R2.2
unnamed: LED2.A, R8.1
unnamed: Q2.1 (G), R3.2
unnamed: Q3.1 (G), R4.2
unnamed: Q4.1 (G), R5.2
SS: CSS.1, U$3.8 (SS)
VOUT: D1.C, D2.C, D3.C, D4.C, JP1.2, JP2.2, JP3.2, JP4.2, SJ5.2, SJ6.2

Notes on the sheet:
Sensor Input
Power In (12V)
12V to 6V Stepdown
Vout Selection
Unpowered SS connectors

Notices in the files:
eda/PDB_MH.brd:
Copyright (c) 2013, Pioneers in Engineering
All rights reserved.
parts and their libraries:
SparkFun-Connectors: Licensing: Creative Commons ShareAlike 4.0 International - https://creativecommons.org/licenses/by-sa/4.0
